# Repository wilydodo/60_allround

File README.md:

I'm making 60% layout keyboard pcb for happyhacking, and other layouts.

can used in dz60 and gh60.

firmware: zmk

used parts
mcu module - E73-2G4M08S1C   
battery charger - TP4054-42-SOT25R   
3.3v regulator - XC6206P332MR-G  
power path diode - BAT54C   
정전기 방지 - SRV05-4A
usb-c -    
도터보드 - Unified Daughterboard   
외부 핀 - 통신용(i2c, spi) 5개, 기타 핀 7개, 전력 3개(gnd, 3v3, 5v)   
추가 핀 커넥터 - JST SH (1.0mm)

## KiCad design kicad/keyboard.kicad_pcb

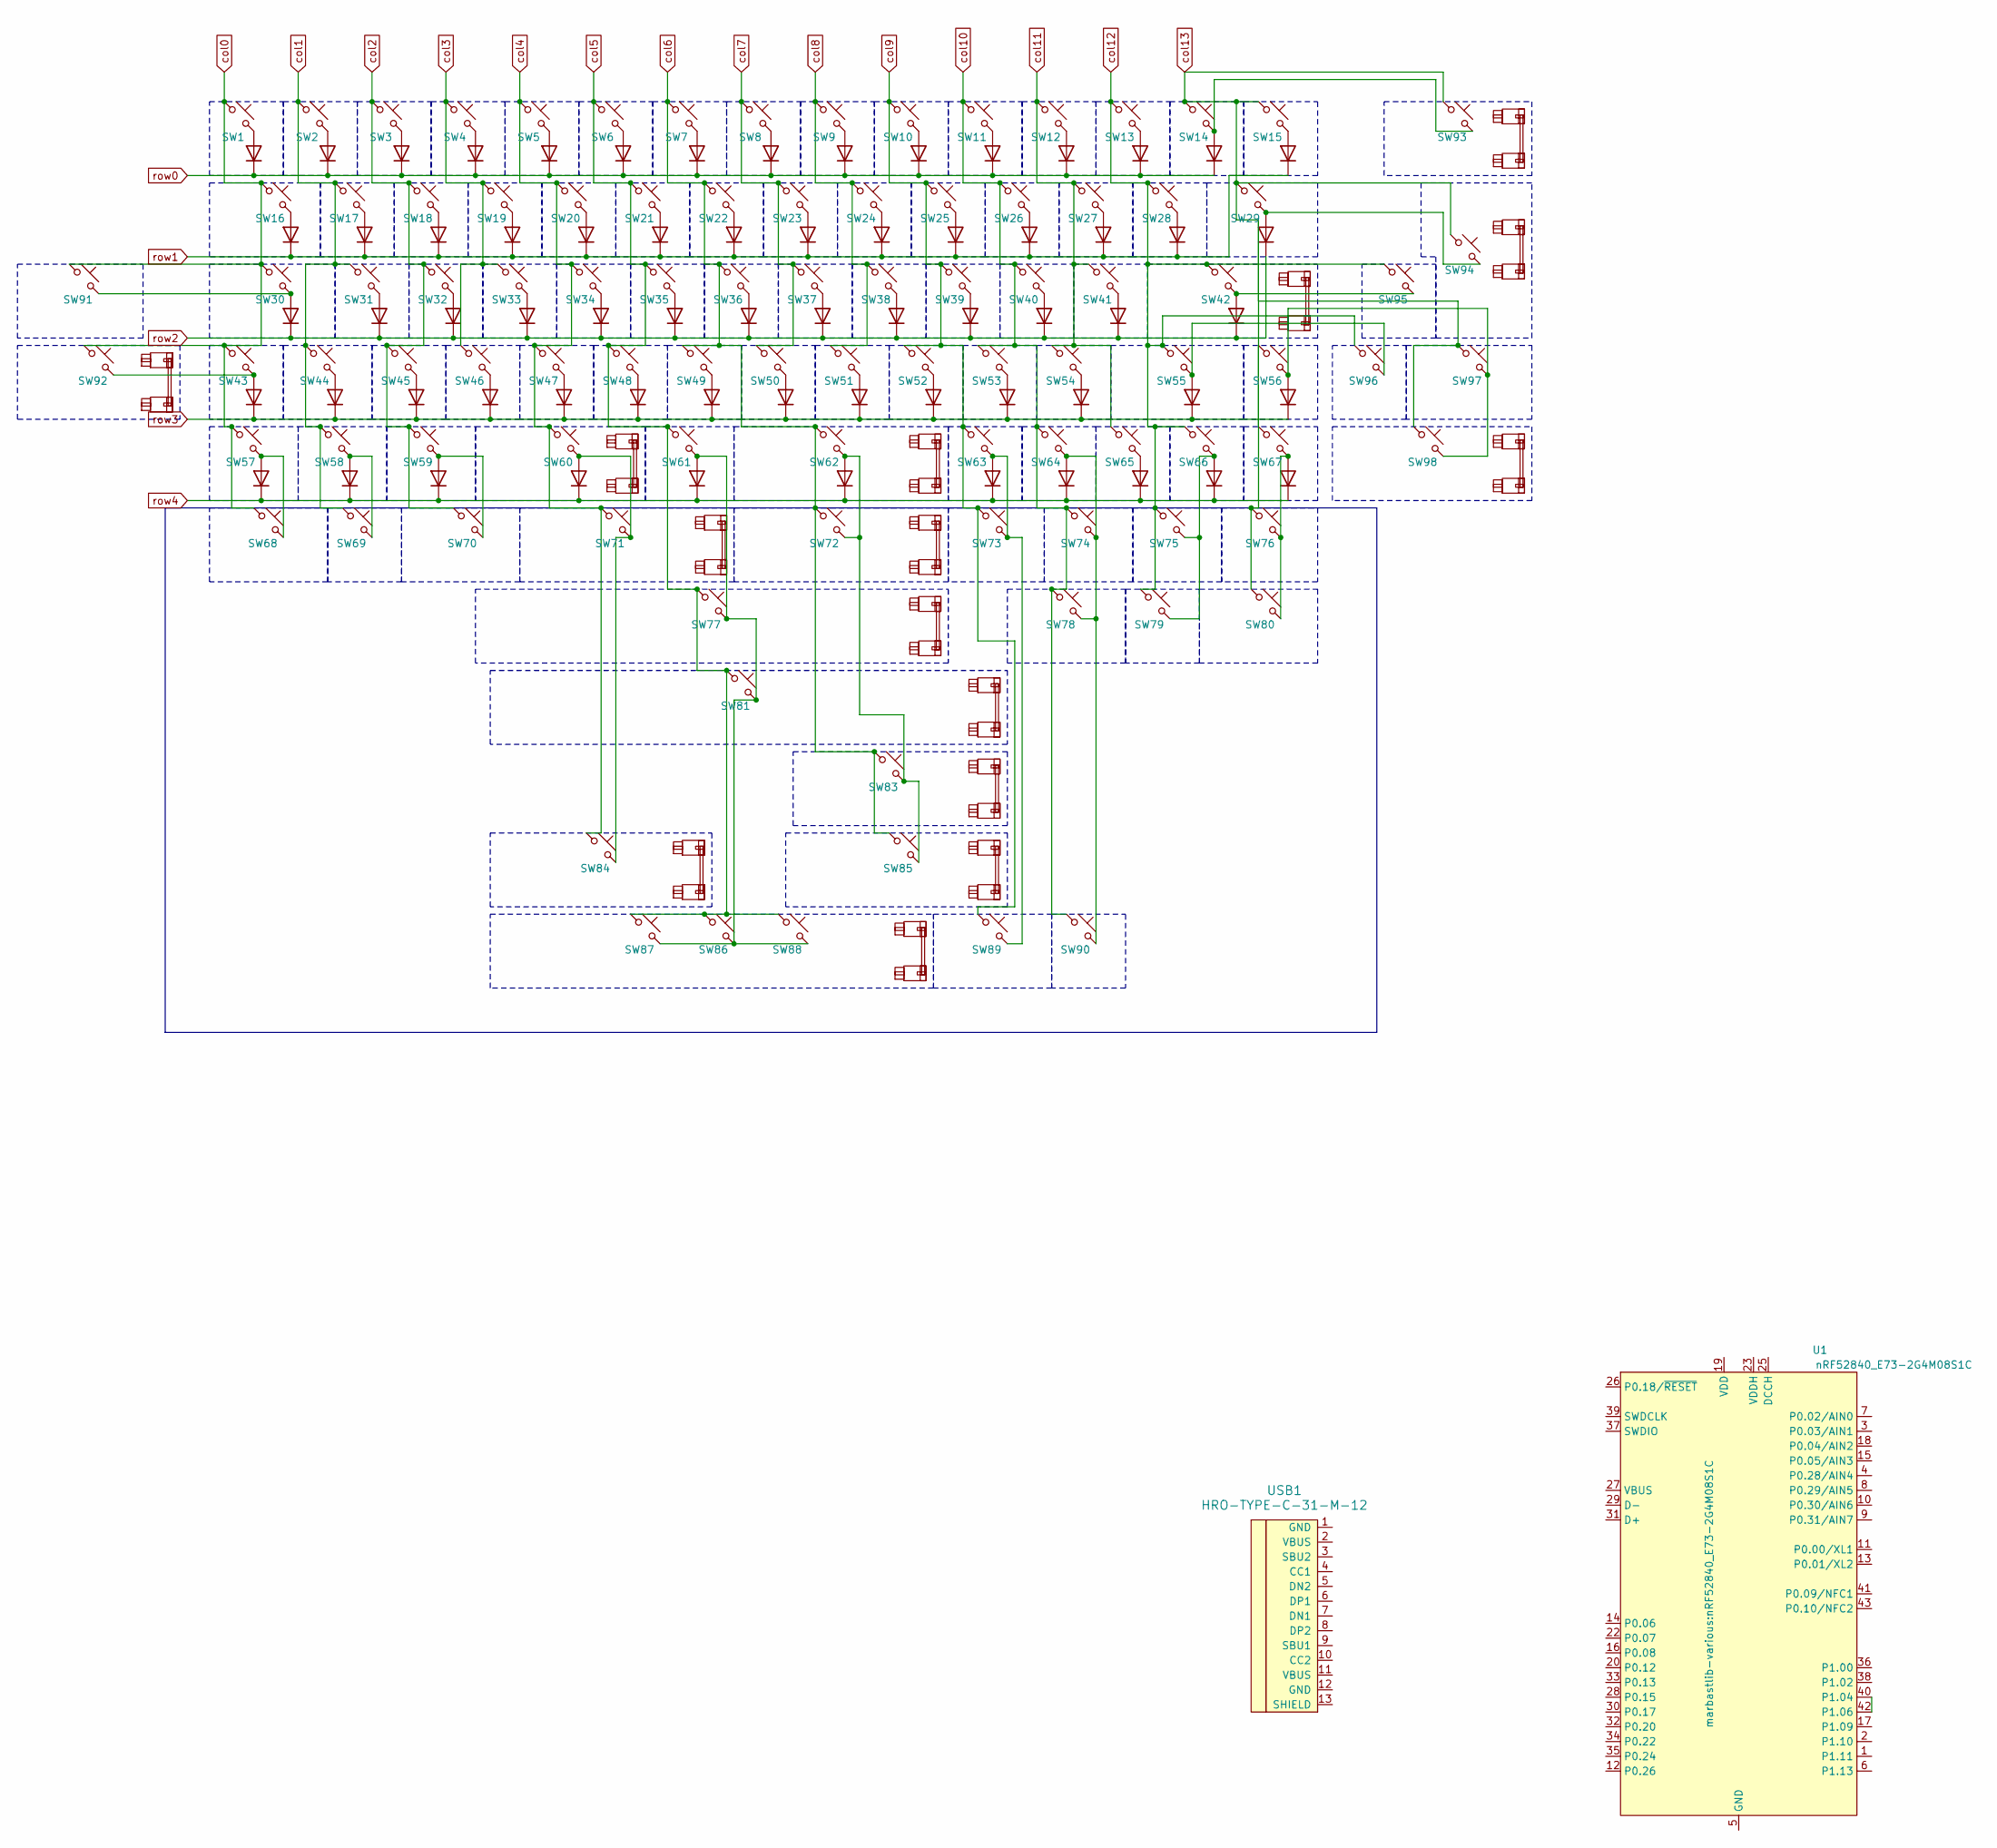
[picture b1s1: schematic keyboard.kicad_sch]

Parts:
D1, D2, D3, D4, D5, D6, D7, D8, D9, D10, D11, D12, D13, D14, D15, D16, D17, D18, D19, D20, D21, D22, D23, D24, D25, D26, D27, D28, D29, D30, D31, D32, D33, D34, D35, D36, D37, D38, D39, D40, D41, D42, D43, D44, D45, D46, D47, D48, D49, D50, D51, D52, D53, D54, D55, D56, D57, D58, D59, D60, D61, D62, D63, D64, D65, D66, D67: 1N4148W; D_SOD-123
S1, S2, S3: MX_stab; STAB_MX_P_2.25u
S4: MX_stab; STAB_MX_P_2u
S5: MX_stab; STAB_MX_P_ISO-ROT
S6, S7, S8, S9, S11: MX_stab; STAB_MX_P_2.75u
S12, S13: MX_stab; STAB_MX_P_3u
S14: MX_stab; STAB_MX_P_6.25u
S15: MX_stab; STAB_MX_P_7u
S16: MX_stab; STAB_MX_P_6u
SW1, SW2, SW3, SW4, SW5, SW6, SW7, SW8, SW9, SW10, SW11, SW12, SW13, SW14, SW15, SW17, SW18, SW19, SW20, SW21, SW22, SW23, SW24, SW25, SW26, SW27, SW28, SW31, SW32, SW33, SW34, SW35, SW36, SW37, SW38, SW39, SW40, SW41, SW42, SW43, SW45, SW46, SW47, SW48, SW49, SW50, SW51, SW52, SW53, SW54, SW56, SW60, SW62, SW63, SW64, SW65, SW66, SW67, SW69, SW71, SW72, SW77, SW79, SW81, SW83, SW84, SW85, SW86, SW87, SW88, SW90, SW91, SW92, SW93, SW94, SW95, SW96, SW98: SW_Push_45deg; SW_MX_1u
SW16, SW29, SW68, SW70, SW78, SW80, SW89: SW_Push_45deg; SW_MX_1.5u
SW30, SW55, SW97: SW_Push_45deg; SW_MX_1.75u
SW44, SW57, SW58, SW59, SW61, SW73, SW74, SW75, SW76: SW_Push_45deg; SW_MX_1.25u
U1: nRF52840_E73-2G4M08S1C; LCSC C356849
USB1: HRO-TYPE-C-31-M-12; HRO-TYPE-C-31-M-12-HandSoldering

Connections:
unnamed: D1.2 (A), SW1.2
unnamed: D2.2 (A), SW2.2
unnamed: D3.2 (A), SW3.2
unnamed: D4.2 (A), SW4.2
unnamed: D5.2 (A), SW5.2
unnamed: D6.2 (A), SW6.2
unnamed: D7.2 (A), SW7.2
unnamed: D8.2 (A), SW8.2
unnamed: D9.2 (A), SW9.2
unnamed: D10.2 (A), SW10.2
unnamed: D11.2 (A), SW11.2
unnamed: D12.2 (A), SW12.2
unnamed: D13.2 (A), SW13.2
unnamed: D14.2 (A), SW14.2, SW93.2
unnamed: D15.2 (A), SW15.2
unnamed: D16.2 (A), SW16.2
unnamed: D17.2 (A), SW17.2
unnamed: D18.2 (A), SW18.2
unnamed: D19.2 (A), SW19.2
unnamed: D20.2 (A), SW20.2
unnamed: D21.2 (A), SW21.2
unnamed: D22.2 (A), SW22.2
unnamed: D23.2 (A), SW23.2
unnamed: D24.2 (A), SW24.2
unnamed: D25.2 (A), SW25.2
unnamed: D26.2 (A), SW26.2
unnamed: D27.2 (A), SW27.2
unnamed: D28.2 (A), SW28.2
unnamed: D29.2 (A), SW29.2, SW94.2
unnamed: D30.2 (A), SW30.2, SW91.2
unnamed: D31.2 (A), SW31.2
unnamed: D32.2 (A), SW32.2
unnamed: D33.2 (A), SW33.2
unnamed: D34.2 (A), SW34.2
unnamed: D35.2 (A), SW35.2
unnamed: D36.2 (A), SW36.2
unnamed: D37.2 (A), SW37.2
unnamed: D38.2 (A), SW38.2
unnamed: D39.2 (A), SW39.2
unnamed: D40.2 (A), SW40.2
unnamed: D41.2 (A), SW41.2
unnamed: D42.2 (A), SW42.2, SW95.2
unnamed: D43.2 (A), SW43.2, SW92.2
unnamed: D44.2 (A), SW44.2
unnamed: D45.2 (A), SW45.2
unnamed: D46.2 (A), SW46.2
unnamed: D47.2 (A), SW47.2
unnamed: D48.2 (A), SW48.2
unnamed: D49.2 (A), SW49.2
unnamed: D50.2 (A), SW50.2
unnamed: D51.2 (A), SW51.2
unnamed: D52.2 (A), SW52.2
unnamed: D53.2 (A), SW53.2
unnamed: D54.2 (A), SW54.2
unnamed: D55.2 (A), SW55.2, SW96.2
unnamed: D56.2 (A), SW56.2, SW97.2, SW98.2
unnamed: D57.2 (A), SW57.2, SW68.2
unnamed: D58.2 (A), SW58.2, SW69.2
unnamed: D59.2 (A), SW59.2, SW70.2
unnamed: D60.2 (A), SW60.2, SW71.2, SW84.2
unnamed: D61.2 (A), SW61.2, SW77.2, SW81.2, SW86.2, SW87.2, SW88.2
unnamed: D62.2 (A), SW62.2, SW72.2, SW83.2, SW85.2
unnamed: D63.2 (A), SW63.2, SW73.2, SW89.2
unnamed: D64.2 (A), SW64.2, SW74.2, SW78.2, SW90.2
unnamed: D65.2 (A), SW65.2
unnamed: D66.2 (A), SW66.2, SW75.2, SW79.2
unnamed: D67.2 (A), SW67.2, SW76.2, SW80.2
unnamed: SW56.1, SW97.1, SW98.1
unnamed: SW67.1, SW76.1, SW80.1
unnamed: U1.5 (GND), U1.21 (GND), U1.24 (GND)
unnamed: U1.40 (P1.04), U1.42 (P1.06)
col0: SW1.1, SW16.1, SW30.1, SW43.1, SW57.1, SW68.1, SW91.1, SW92.1
col1: SW2.1, SW17.1, SW31.1, SW44.1, SW58.1, SW69.1
col2: SW3.1, SW18.1, SW32.1, SW45.1, SW59.1, SW70.1
col3: SW4.1, SW19.1, SW33.1, SW46.1
col4: SW5.1, SW20.1, SW34.1, SW47.1, SW60.1, SW71.1, SW84.1
col5: SW6.1, SW21.1, SW35.1, SW48.1, SW61.1, SW77.1, SW81.1, SW86.1, SW87.1, SW88.1
col6: SW7.1, SW22.1, SW36.1, SW49.1, SW62.1, SW72.1, SW83.1, SW85.1
col7: SW8.1, SW23.1, SW37.1, SW50.1
col8: SW9.1, SW24.1, SW38.1, SW51.1
col9: SW10.1, SW25.1, SW39.1, SW52.1, SW63.1, SW73.1, SW89.1
col10: SW11.1, SW26.1, SW40.1, SW53.1, SW64.1, SW74.1, SW78.1, SW90.1
col11: SW12.1, SW27.1, SW41.1, SW54.1, SW65.1
col12: SW13.1, SW28.1, SW42.1, SW55.1, SW66.1, SW75.1, SW79.1, SW95.1, SW96.1
col13: SW14.1, SW15.1, SW29.1, SW93.1, SW94.1
row0: D1.1 (K), D2.1 (K), D3.1 (K), D4.1 (K), D5.1 (K), D6.1 (K), D7.1 (K), D8.1 (K), D9.1 (K), D10.1 (K), D11.1 (K), D12.1 (K), D13.1 (K), D14.1 (K)
row1: D15.1 (K), D16.1 (K), D17.1 (K), D18.1 (K), D19.1 (K), D20.1 (K), D21.1 (K), D22.1 (K), D23.1 (K), D24.1 (K), D25.1 (K), D26.1 (K), D27.1 (K), D28.1 (K)
row2: D29.1 (K), D30.1 (K), D31.1 (K), D32.1 (K), D33.1 (K), D34.1 (K), D35.1 (K), D36.1 (K), D37.1 (K), D38.1 (K), D39.1 (K), D40.1 (K), D41.1 (K), D42.1 (K)
row3: D43.1 (K), D44.1 (K), D45.1 (K), D46.1 (K), D47.1 (K), D48.1 (K), D49.1 (K), D50.1 (K), D51.1 (K), D52.1 (K), D53.1 (K), D54.1 (K), D55.1 (K), D56.1 (K)
row4: D57.1 (K), D58.1 (K), D59.1 (K), D60.1 (K), D61.1 (K), D62.1 (K), D63.1 (K), D64.1 (K), D65.1 (K), D66.1 (K), D67.1 (K)

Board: 2 copper layers, 188 parts (2 on the bottom side), 90 nets, no tracks yet.

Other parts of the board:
HOLE: VAL**; PKRHC
HOLE#2, HOLE#4, HOLE#5: VAL**; PKRH
HOLE#3, HOLE#6, HOLE#7: VAL**; PKRHSL

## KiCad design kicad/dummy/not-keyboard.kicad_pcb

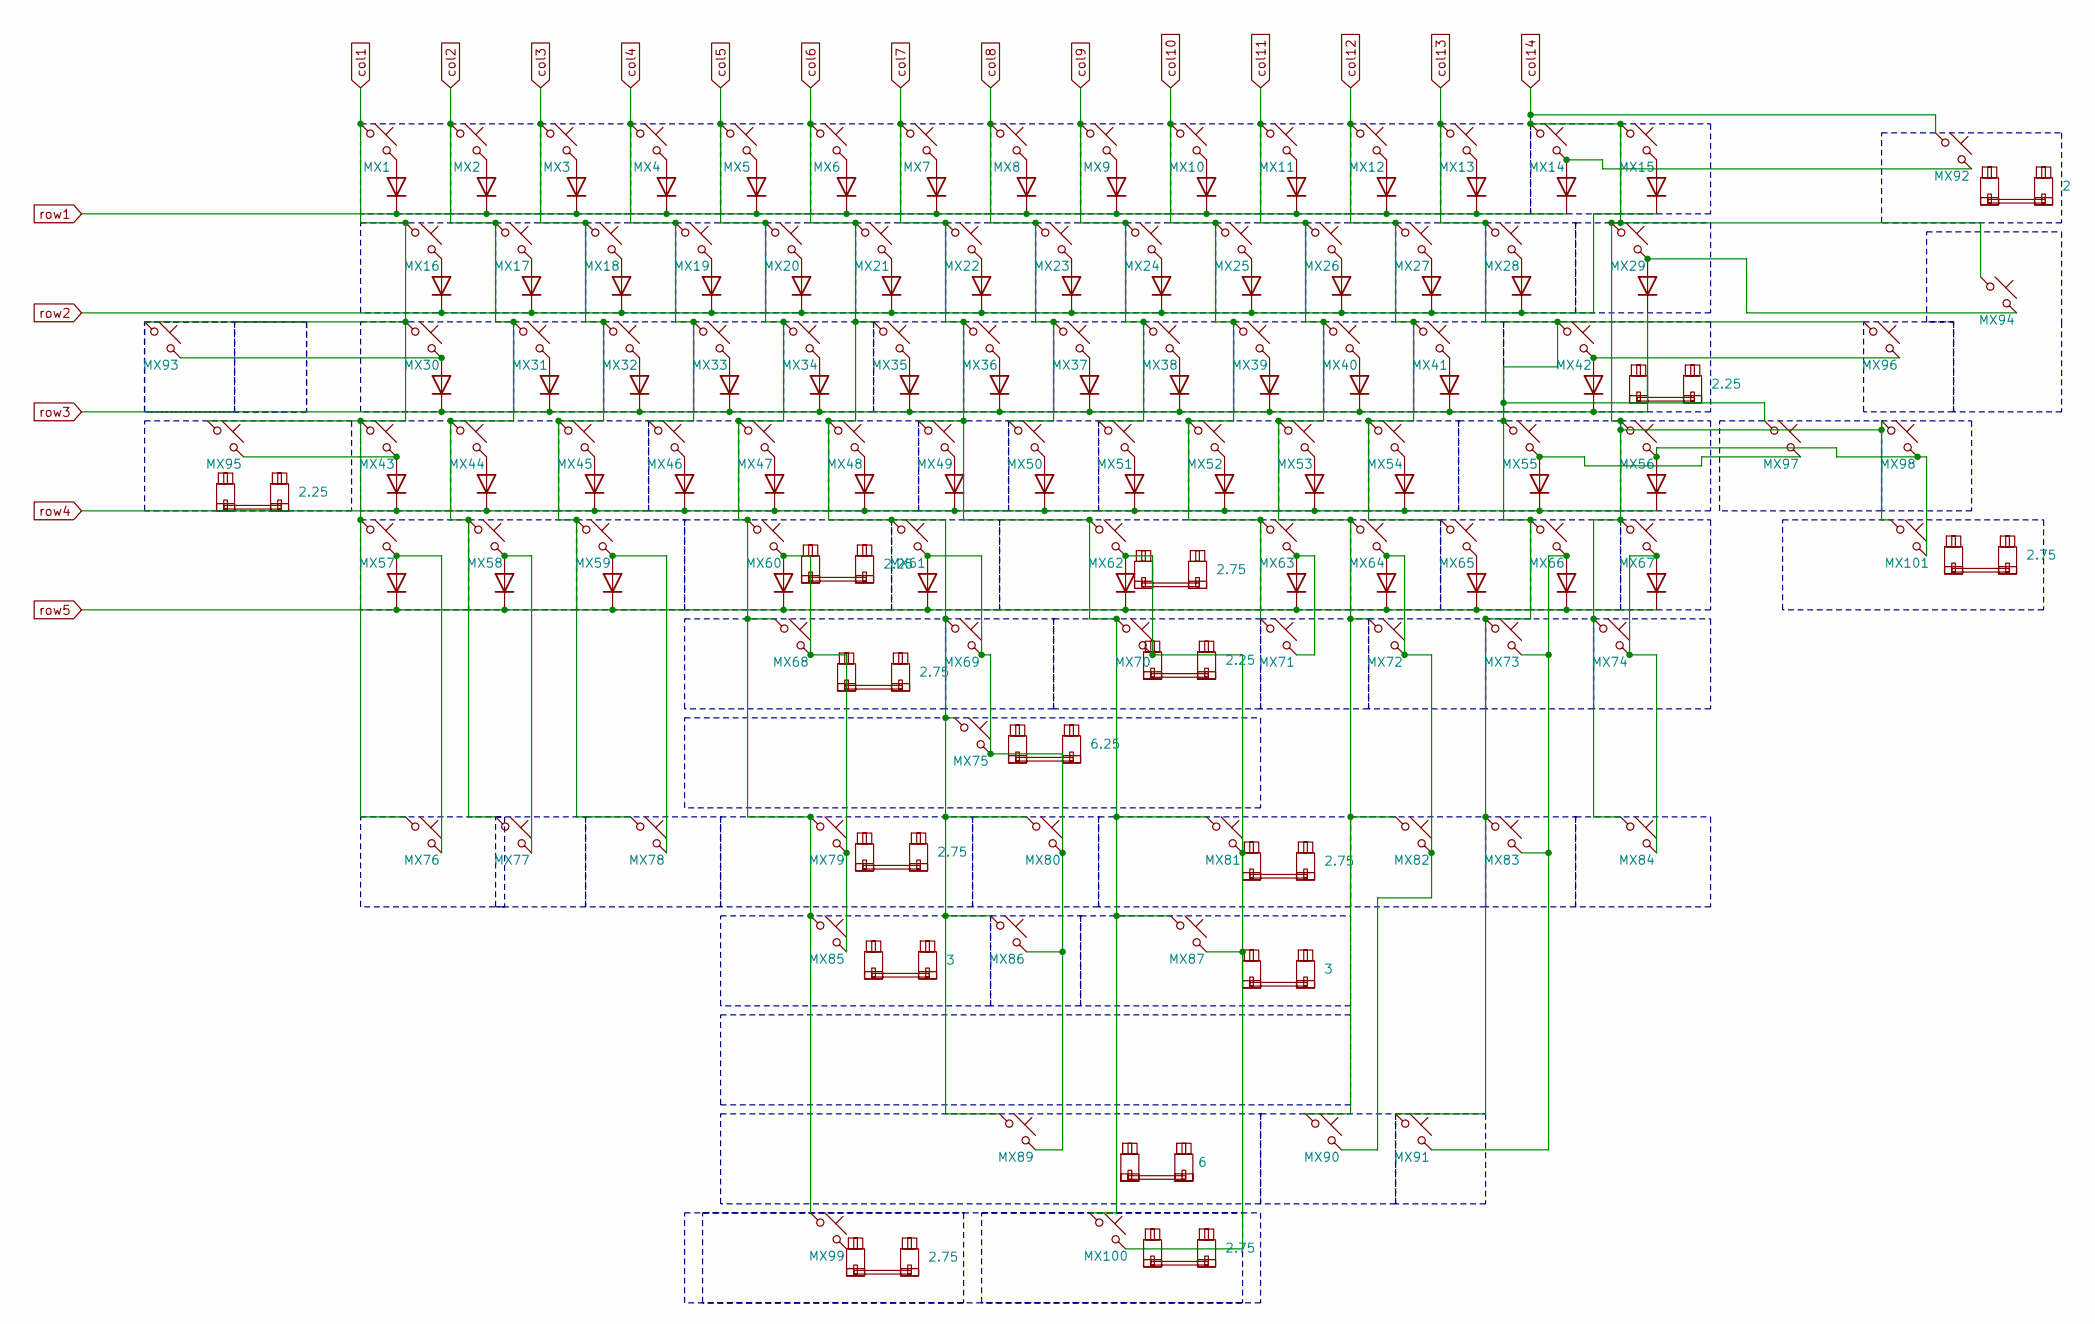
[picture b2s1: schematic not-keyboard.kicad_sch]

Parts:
D1, D2, D3, D4, D5, D6, D7, D8, D9, D10, D11, D12, D13, D14, D15, D16, D17, D18, D19, D20, D21, D22, D23, D24, D25, D26, D27, D28, D29, D30, D31, D32, D33, D34, D35, D36, D37, D38, D39, D40, D41, D42, D43, D44, D45, D46, D47, D48, D49, D50, D51, D52, D53, D54, D55, D56, D57, D58, D59, D60, D61, D62, D63, D64, D65, D66, D67: 1N4148W; D_SOD-123
MX1, MX2, MX3, MX4, MX5, MX6, MX7, MX8, MX9, MX10, MX11, MX12, MX13, MX14, MX15, MX17, MX18, MX19, MX20, MX21, MX22, MX23, MX24, MX25, MX26, MX27, MX28, MX29, MX31, MX32, MX33, MX34, MX35, MX36, MX37, MX38, MX39, MX40, MX41, MX42, MX43, MX45, MX46, MX47, MX48, MX49, MX50, MX51, MX52, MX53, MX54, MX56, MX60, MX62, MX63, MX64, MX65, MX66, MX67, MX68, MX70, MX75, MX77, MX79, MX81, MX83, MX85, MX86, MX87, MX89, MX91, MX92, MX93, MX94, MX95, MX96, MX98, MX99, MX100, MX101: MX_SW_HS; SW_MX_1u
MX16, MX76, MX78, MX80, MX82, MX84, MX90: MX_SW_HS; SW_MX_1.5u
MX30, MX55, MX97: MX_SW_HS; SW_MX_1.75u
MX44, MX57, MX58, MX59, MX61, MX69, MX71, MX72, MX73, MX74: MX_SW_HS; SW_MX_1.25u
S1, S2, S5, S15: 2.25; STAB_MX_P_2.25u
S3, S4, S7, S8, S13, S14, S18: 2.75; STAB_MX_P_2.75u
S6: 6.25; STAB_MX_P_6.25u
S9, S10: 3; STAB_MX_P_3u
S12: 6; STAB_MX_P_6u
S16: 2; STAB_MX_P_2u

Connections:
unnamed: D1.2 (A), MX1.2
unnamed: D2.2 (A), MX2.2
unnamed: D3.2 (A), MX3.2
unnamed: D4.2 (A), MX4.2
unnamed: D5.2 (A), MX5.2
unnamed: D6.2 (A), MX6.2
unnamed: D7.2 (A), MX7.2
unnamed: D8.2 (A), MX8.2
unnamed: D9.2 (A), MX9.2
unnamed: D10.2 (A), MX10.2
unnamed: D11.2 (A), MX11.2
unnamed: D12.2 (A), MX12.2
unnamed: D13.2 (A), MX13.2
unnamed: D14.2 (A), MX14.2, MX92.2
unnamed: D15.2 (A), MX15.2
unnamed: D16.2 (A), MX16.2
unnamed: D17.2 (A), MX17.2
unnamed: D18.2 (A), MX18.2
unnamed: D19.2 (A), MX19.2
unnamed: D20.2 (A), MX20.2
unnamed: D21.2 (A), MX21.2
unnamed: D22.2 (A), MX22.2
unnamed: D23.2 (A), MX23.2
unnamed: D24.2 (A), MX24.2
unnamed: D25.2 (A), MX25.2
unnamed: D26.2 (A), MX26.2
unnamed: D27.2 (A), MX27.2
unnamed: D28.2 (A), MX28.2
unnamed: D29.2 (A), MX29.2, MX94.2
unnamed: D30.2 (A), MX30.2, MX93.2
unnamed: D31.2 (A), MX31.2
unnamed: D32.2 (A), MX32.2
unnamed: D33.2 (A), MX33.2
unnamed: D34.2 (A), MX34.2
unnamed: D35.2 (A), MX35.2
unnamed: D36.2 (A), MX36.2
unnamed: D37.2 (A), MX37.2
unnamed: D38.2 (A), MX38.2
unnamed: D39.2 (A), MX39.2
unnamed: D40.2 (A), MX40.2
unnamed: D41.2 (A), MX41.2
unnamed: D42.2 (A), MX42.2, MX96.2
unnamed: D43.2 (A), MX43.2, MX95.2
unnamed: D44.2 (A), MX44.2
unnamed: D45.2 (A), MX45.2
unnamed: D46.2 (A), MX46.2
unnamed: D47.2 (A), MX47.2
unnamed: D48.2 (A), MX48.2
unnamed: D49.2 (A), MX49.2
unnamed: D50.2 (A), MX50.2
unnamed: D51.2 (A), MX51.2
unnamed: D52.2 (A), MX52.2
unnamed: D53.2 (A), MX53.2
unnamed: D54.2 (A), MX54.2
unnamed: D55.2 (A), MX55.2, MX97.2
unnamed: D56.2 (A), MX56.2, MX98.2, MX101.2
unnamed: D57.2 (A), MX57.2, MX76.2
unnamed: D58.2 (A), MX58.2, MX77.2
unnamed: D59.2 (A), MX59.2, MX78.2
unnamed: D60.2 (A), MX60.2, MX68.2, MX79.2, MX85.2
unnamed: D61.2 (A), MX61.2, MX69.2, MX75.2, MX80.2, MX86.2, MX89.2
unnamed: D62.2 (A), MX62.2, MX70.2, MX81.2, MX87.2, MX100.2
unnamed: D63.2 (A), MX63.2, MX71.2
unnamed: D64.2 (A), MX64.2, MX72.2, MX82.2, MX90.2
unnamed: D65.2 (A), MX65.2
unnamed: D66.2 (A), MX66.2, MX73.2, MX83.2, MX91.2
unnamed: D67.2 (A), MX67.2, MX74.2, MX84.2
col1: MX1.1, MX16.1, MX30.1, MX43.1, MX57.1, MX76.1, MX93.1, MX95.1
col2: MX2.1, MX17.1, MX31.1, MX44.1, MX58.1, MX77.1
col3: MX3.1, MX18.1, MX32.1, MX45.1, MX59.1, MX78.1
col4: MX4.1, MX19.1, MX33.1, MX46.1
col5: MX5.1, MX20.1, MX34.1, MX47.1, MX60.1, MX68.1, MX79.1, MX85.1, MX99.1
col6: MX6.1, MX21.1, MX35.1, MX48.1, MX61.1, MX69.1, MX75.1, MX80.1, MX86.1, MX89.1
col7: MX7.1, MX22.1, MX36.1, MX49.1, MX62.1, MX70.1, MX81.1, MX87.1, MX100.1
col8: MX8.1, MX23.1, MX37.1, MX50.1
col9: MX9.1, MX24.1, MX38.1, MX51.1
col10: MX10.1, MX25.1, MX39.1, MX52.1, MX63.1, MX71.1
col11: MX11.1, MX26.1, MX40.1, MX53.1, MX64.1, MX72.1, MX82.1, MX90.1
col12: MX12.1, MX27.1, MX41.1, MX54.1, MX65.1
col13: MX13.1, MX28.1, MX42.1, MX55.1, MX66.1, MX73.1, MX83.1, MX91.1, MX96.1, MX97.1
col14: MX14.1, MX15.1, MX29.1, MX56.1, MX67.1, MX74.1, MX84.1, MX92.1, MX94.1, MX98.1, MX101.1
row1: D1.1 (K), D2.1 (K), D3.1 (K), D4.1 (K), D5.1 (K), D6.1 (K), D7.1 (K), D8.1 (K), D9.1 (K), D10.1 (K), D11.1 (K), D12.1 (K), D13.1 (K), D14.1 (K)
row2: D15.1 (K), D16.1 (K), D17.1 (K), D18.1 (K), D19.1 (K), D20.1 (K), D21.1 (K), D22.1 (K), D23.1 (K), D24.1 (K), D25.1 (K), D26.1 (K), D27.1 (K), D28.1 (K)
row3: D29.1 (K), D30.1 (K), D31.1 (K), D32.1 (K), D33.1 (K), D34.1 (K), D35.1 (K), D36.1 (K), D37.1 (K), D38.1 (K), D39.1 (K), D40.1 (K), D41.1 (K), D42.1 (K)
row4: D43.1 (K), D44.1 (K), D45.1 (K), D46.1 (K), D47.1 (K), D48.1 (K), D49.1 (K), D50.1 (K), D51.1 (K), D52.1 (K), D53.1 (K), D54.1 (K), D55.1 (K), D56.1 (K)
row5: D57.1 (K), D58.1 (K), D59.1 (K), D60.1 (K), D61.1 (K), D62.1 (K), D63.1 (K), D64.1 (K), D65.1 (K), D66.1 (K), D67.1 (K)

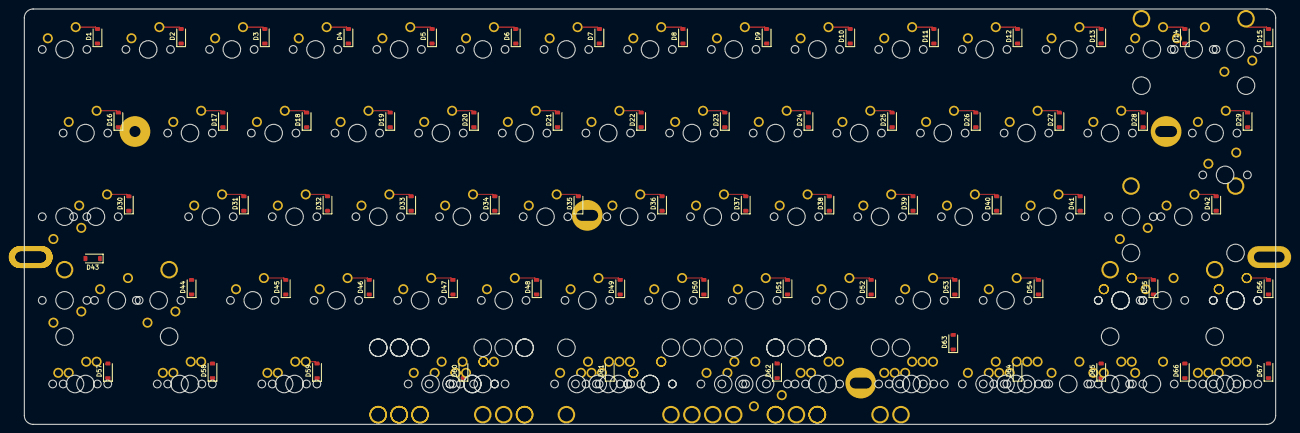
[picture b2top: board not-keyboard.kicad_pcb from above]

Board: 2 copper layers, 285.0 x 94.6 mm, 190 parts (0 on the bottom side), 86 nets.

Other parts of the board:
HOLE: VAL**; PKRHC
HOLE#2, HOLE#4, HOLE#5: VAL**; PKRH
HOLE#3, HOLE#6, HOLE#7: VAL**; PKRHSL

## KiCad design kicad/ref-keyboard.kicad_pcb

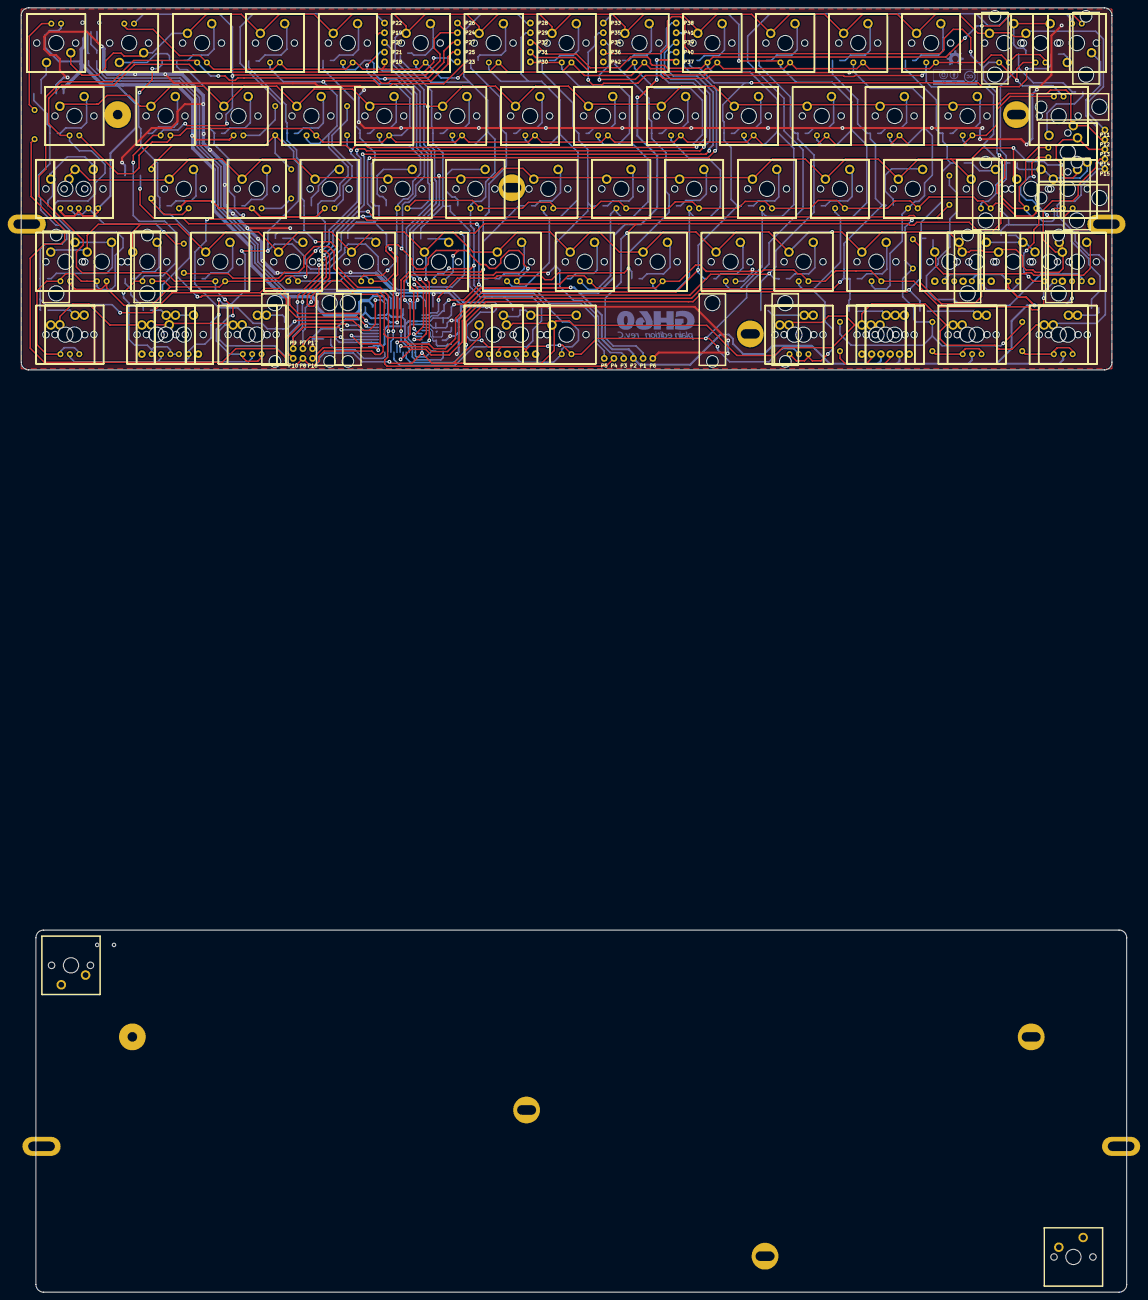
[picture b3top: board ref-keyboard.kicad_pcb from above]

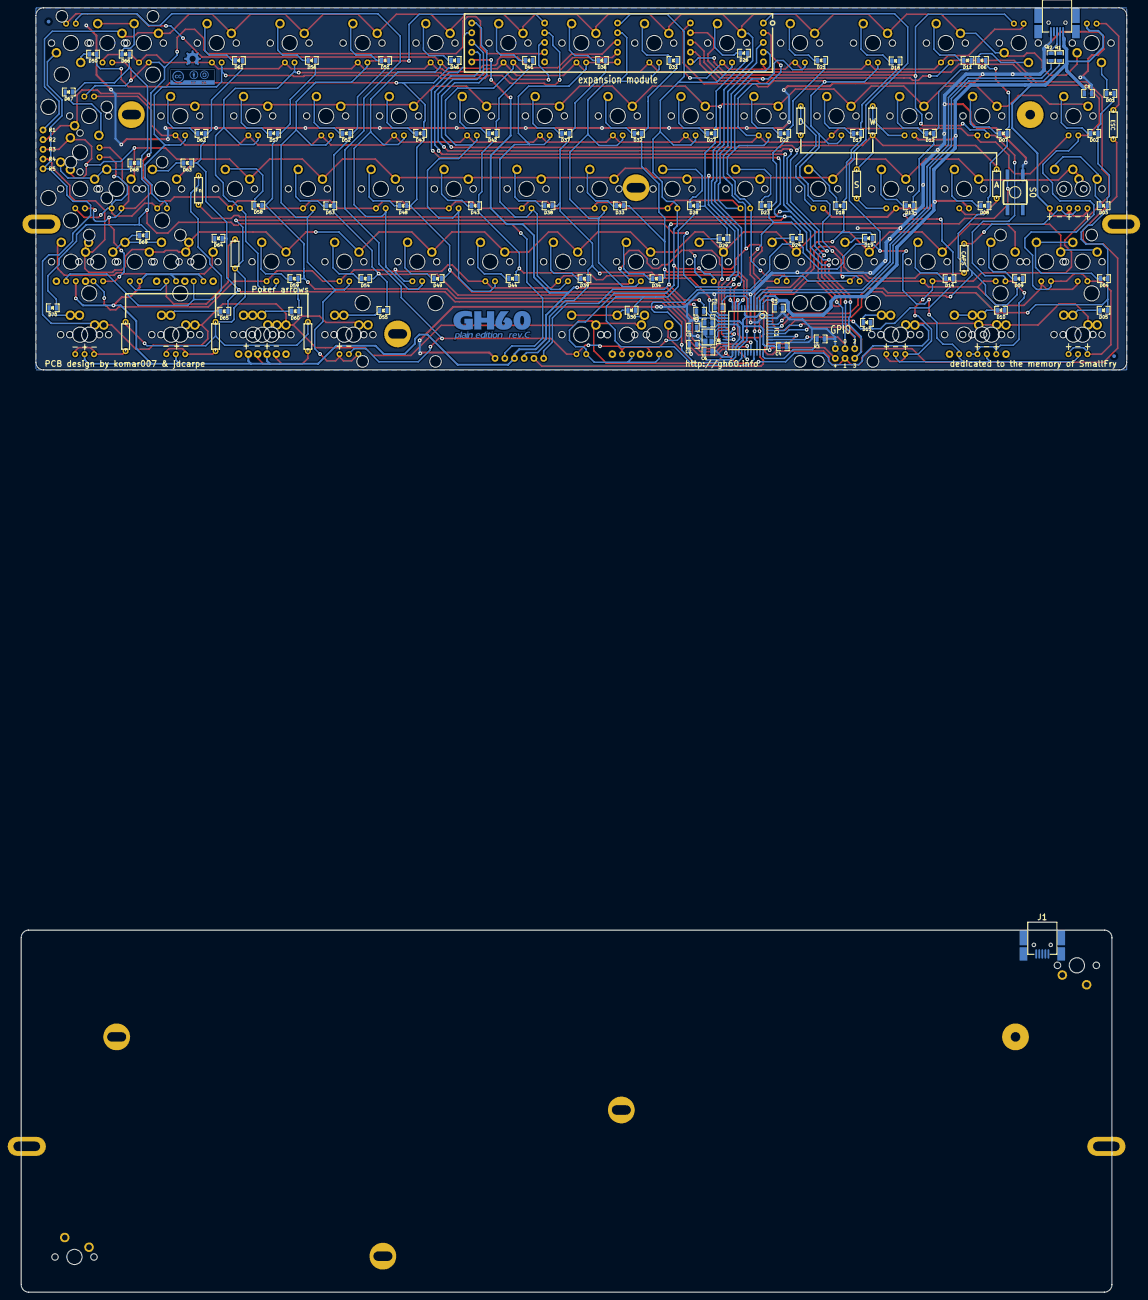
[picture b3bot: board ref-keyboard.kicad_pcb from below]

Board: 2 copper layers, 285.0 x 94.6 mm, 344 parts (95 on the bottom side), 130 nets.

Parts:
C1, C2: 22p; 0805C
C3, C8: 1u; 0805C
C4, C5, C6, C7: 100n; 0805C
D01, D02, D03, D04, D05, D06, D07, D08, D09, D10, D11, D12, D13, D14, D15, D16, D17, D18, D19, D21, D22, D23, D24, D26, D27, D28, D29, D30, D31, D32, D33, D34, D36, D37, D38, D39, D41, D42, D43, D44, D46, D47, D48, D49, D50, D51, D52, D53, D54, D55, D56, D57, D58, D59, D60, D61, D62, D63, D64, D65, D66, D67, D68, D69, D70: 1N4148; 0805D
DB02, DB04, DB06, DB07, DB09, DB11, DB14, DB16, DB17, DB19, DB21, DB22, DB23, DB24, DB26, DB27, DB28, DB29, DB30, DB31, DB32, DB33, DB34, DB36, DB37, DB38, DB39, DB41, DB041, DB42, DB43, DB44, DB46, DB47, DB48, DB49, DB50, DB51, DB52, DB53, DB54, DB56, DB57, DB58, DB59, DB61, DB62, DB63, DB66, DB67, DB68, DB69, DB301, DB302, DB661, DB681, DB682: LED; MX1A-led_no3d
DB05, DB10, DB15, DB051, DB55, DB101, DB102, DB151, DB551: LEDa; MX1A-led
DC1, DC2: LED; MX1A-led_no3d
DC3: LED; MX1A-ledlock
DF3, DF10, DF11, DF20, DF201: LED; MX1A-led_no3d
DF21, DF22, DF23, DF211, DF221, DF231, DF232: LEDa; MX1A-led
DW1, DW2, DW3, DW4: LED; MX1A-led_no3d
FID: FIDUCIAL
FID#2: FIDUCIAL
HOLE: VAL**; PKRHSL
HOLE#2, HOLE#4, HOLE#6, HOLE#8, HOLE#11, HOLE#12: VAL**; PKRH
HOLE#3, HOLE#7, HOLE#9: VAL**; PKRHSL
HOLE#5, HOLE#10: VAL**; PKRHC
IC1: ATMEGA32U4; TQFP44
J1, J1#2: MINI; 67503
MXST: VAL**; MXST
MXST#2, MXST#3, MXST#4, MXST#5, MXST#6, MXST#7, MXST#8, MXST#9, MXST#10, MXST#11, MXST#12, MXST#13, MXST#14, MXST#15: VAL**; MXST
MXWIRE: VAL**; MX1A-wire
MXWIRE#2, MXWIRE#3, MXWIRE#4, MXWIRE#5, MXWIRE#6, MXWIRE#7, MXWIRE#8, MXWIRE#9: VAL**; MX1A-wire
P1, P2, P3, P4, P5, P6, P7, P8, P9, P10, P11, P12, P13, P14, P15, P16, P17, P18, P19, P20, P21, P22, P23, P24, P25, P26, P27, P28, P29, P30, P31, P32, P33, P34, P35, P36, P37, P38, P39, P40, P41, P42: CONN_1; pad
R1, R2: 22; 0805R
R3, R5: 10k; 0805R
R4: 300; resistor
R6, R7, R8, R9, R10, R11, R12, R13, R14, R15: R; resistor
S0: DTSM-6; KSEM31GLFS
S01, S01#2, S02, S03, S04, S05, S06, S07, S08, S10, S11, S12, S13, S14, S15, S16, S17, S18, S19, S21, S22, S23, S24, S26, S27, S28, S29, S30, S31, S32, S33, S34, S36, S37, S38, S39, S41, S42, S43, S44, S46, S47, S48, S49, S51, S52, S53, S54, S55, S56, S57, S58, S59, S60, S61, S62, S65, S66, S67, S68, S69, S70: MX1A
S09, S031, S041, S50, S63, S101, S102, S151, S301, S302, S0512, S552, S601, S602, S641, S661, S682, S691, S692, S6512, S7012, S7012#2: MX1Aa; MX1A_no3d
S64, S681: MX1A; MX1A_no3d
X1: ASX3F; 4-SMD

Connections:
/GPIO0: IC1.36, P7.1, P38.1, R6.1, R7.1, R8.1, R9.1
/GPIO1: IC1.37, P8.1, P39.1, R12.1
/GPIO2: IC1.38, P9.1, P40.1, R10.1
/GPIO3: IC1.39, P10.1, P41.1, R11.1, R13.1, R14.1, R15.1
/Leds/lcol1: DB02.1, DB04.1, DB05.1, DB041.1, DB051.1, P23.1
/Leds/lcol2: DB06.1, DB07.1, DB09.1, DB10.1, DB101.1, DB102.1, P24.1
/Leds/lcol3: DB11.1, DB14.1, DB15.1, DB151.1, P25.1
/Leds/lcol4: DB16.1, DB17.1, DB19.1, P26.1
/Leds/lcol5: DB21.1, DB22.1, DB23.1, DB24.1, P27.1
/Leds/lcol6: DB26.1, DB27.1, DB28.1, DB29.1, DB30.1, DB301.1, DB302.1, P28.1
/Leds/lcol7: DB31.1, DB32.1, DB33.1, DB34.1, P29.1
/Leds/lcol8: DB36.1, DB37.1, DB38.1, DB39.1, P30.1
/Leds/lcol9: DB41.1, DB42.1, DB43.1, DB44.1, P31.1
/Leds/lcol10: DB46.1, DB47.1, DB48.1, DB49.1, DB50.1, P32.1
/Leds/lcol11: DB51.1, DB52.1, DB53.1, DB54.1, DB55.1, DB551.1, P33.1
/Leds/lcol12: DB56.1, DB57.1, DB58.1, DB59.1, P34.1
/Leds/lcol13: DB61.1, DB62.1, DB63.1, P35.1
/Leds/lcol14: DB66.1, DB67.1, DB68.1, DB69.1, DB661.1, DB681.1, DB682.1, P36.1
/Leds/lrow1: DB06.2, DB11.2, DB16.2, DB21.2, DB26.2, DB31.2, DB36.2, DB41.2, DB46.2, DB51.2, DB56.2, DB61.2, DB66.2, DB661.2, P18.1
/Leds/lrow2: DB02.2, DB07.2, DB17.2, DB22.2, DB27.2, DB32.2, DB37.2, DB42.2, DB47.2, DB52.2, DB57.2, DB62.2, DB67.2, P19.1
/Leds/lrow3: DB23.2, DB28.2, DB33.2, DB38.2, DB43.2, DB48.2, DB53.2, DB58.2, DB63.2, DB68.2, DB681.2, DB682.2, P20.1
/Leds/lrow4: DB04.2, DB09.2, DB14.2, DB19.2, DB24.2, DB29.2, DB34.2, DB39.2, DB041.2, DB44.2, DB49.2, DB54.2, DB59.2, DB69.2, P21.1
/Leds/lrow5: DB05.2, DB10.2, DB15.2, DB30.2, DB50.2, DB55.2, DB102.2, DB301.2, DB302.2, P22.1
/Matrix/CAPS_LED: IC1.10, P4.1, R4.2
/Matrix/col1: D01.1, D02.1, D03.1, D04.1, D05.1, IC1.41
/Matrix/col2: D06.1, D07.1, D08.1, D09.1, D10.1, IC1.40
/Matrix/col3: D11.1, D12.1, D13.1, D14.1, D15.1, IC1.1
/Matrix/col4: D16.1, D17.1, D18.1, D19.1, IC1.32
/Matrix/col5: D21.1, D22.1, D23.1, D24.1, IC1.31
/Matrix/col6: D26.1, D27.1, D28.1, D29.1, D30.1, IC1.30
/Matrix/col7: D31.1, D32.1, D33.1, D34.1, IC1.25
/Matrix/col8: D36.1, D37.1, D38.1, D39.1, IC1.9, P3.1
/Matrix/col9: D41.1, D42.1, D43.1, D44.1, IC1.12
/Matrix/col10: D46.1, D47.1, D48.1, D49.1, D50.1, IC1.29
/Matrix/col11: D51.1, D52.1, D53.1, D54.1, D55.1, IC1.28
/Matrix/col12: D56.1, D57.1, D58.1, D59.1, D60.1, IC1.27
/Matrix/col13: D61.1, D62.1, D63.1, D64.1, D65.1, IC1.26
/Matrix/col14: D66.1, D67.1, D68.1, D69.1, D70.1, IC1.11, P1.1
/Matrix/row1: IC1.18, P11.1, S01.1, S06.1, S11.1, S16.1, S21.1, S26.1, S31.1, S36.1, S41.1, S46.1, S51.1, S56.1, S61.1, S66.1, S661.1
/Matrix/row2: IC1.19, P12.1, S02.1, S07.1, S12.1, S17.1, S22.1, S27.1, S32.1, S37.1, S42.1, S47.1, S52.1, S57.1, S62.1, S67.1
/Matrix/row3: IC1.20, P13.1, S03.1, S08.1, S13.1, S18.1, S23.1, S28.1, S031.2, S33.1, S38.1, S43.1, S48.1, S53.1, S58.1, S63.1, S68.1, S681.1, S682.2
/Matrix/row4: IC1.21, P14.1, S04.1, S09.1, S14.1, S19.1, S24.1, S29.1, S34.1, S39.1, S041.1, S44.1, S49.1, S54.1, S59.1, S64.2, S69.1, S641.1, S691.2, S692.1
/Matrix/row5: IC1.22, P15.1, S05.1, S10.1, S15.1, S30.1, S50.1, S55.1, S60.1, S65.1, S70.1, S101.1, S102.1, S151.1, S301.1, S302.1, S0512.1, S552.1, S601.1, S602.1, S6512.1, S7012.1, S7012#2.1
/~RES: IC1.13, P5.1, R5.2, S0.3
GND: C1.2, C2.2, C3.2, C4.2, C5.2, C6.2, C7.2, C8.2, IC1.5, IC1.15, IC1.23, IC1.35, IC1.43, J1.5, J1#2.5, P6.1, P17.1, P42.1, R3.2, S0.1, X1.2, X1.4
unnamed: C1.1, IC1.16, X1.1
unnamed: DW3.2, R8.2
unnamed: DW2.2, R7.2
unnamed: DW1.2, R6.2
unnamed: DW4.2, R9.2
unnamed: IC1.33, R3.1
unnamed: J1.3, J1#2.3, R2.2
unnamed: J1.2, J1#2.2, R1.2
unnamed: IC1.4, R2.1
unnamed: IC1.3, R1.1
unnamed: C3.1, IC1.6
unnamed: C2.1, IC1.17, X1.3
unnamed: DF22.2, DF221.2, R14.2
unnamed: DF3.2, R12.2
unnamed: DF10.2, DF11.2, R10.2
unnamed: DF23.2, DF231.2, R15.2
unnamed: DF20.2, DF201.2, R11.2
unnamed: DF21.2, DF211.2, R13.2
unnamed: D16.2, S16.2
unnamed: D27.2, S27.2
unnamed: D28.2, S28.2
unnamed: D29.2, S29.2
unnamed: D17.2, S17.2
unnamed: D18.2, S18.2
unnamed: D19.2, S19.2
unnamed: D41.2, S41.2
unnamed: D37.2, S37.2
unnamed: D38.2, S38.2
unnamed: D22.2, S22.2
unnamed: D43.2, S43.2
unnamed: D42.2, S42.2
unnamed: D46.2, S46.2
unnamed: D47.2, S47.2
unnamed: D23.2, S23.2
unnamed: D21.2, S21.2
unnamed: D31.2, S31.2
unnamed: D01.2, S01.2
unnamed: D33.2, S33.2
unnamed: D32.2, S32.2
unnamed: D36.2, S36.2
unnamed: D05.2, S05.2, S0512.2
unnamed: D15.2, S15.2, S151.2
unnamed: D55.2, S55.2, S552.2
unnamed: D51.2, S51.2
unnamed: D65.2, S65.2, S6512.2
unnamed: D12.2, S12.2
unnamed: D02.2, S02.2
unnamed: D07.2, S07.2
unnamed: D08.2, S08.2
unnamed: D13.2, S13.2
unnamed: D09.2, S09.2
unnamed: D14.2, S14.2
unnamed: D70.2, S70.2, S7012.2, S7012#2.2
unnamed: D03.2, S03.2, S031.1
unnamed: D26.2, S26.2
unnamed: D06.2, S06.2
unnamed: D11.2, S11.2
unnamed: D50.2, S50.2
unnamed: D63.2, S63.2
unnamed: D58.2, S58.2
unnamed: D53.2, S53.2
unnamed: D67.2, S67.2
unnamed: D52.2, S52.2
unnamed: D48.2, S48.2
unnamed: D44.2, S44.2
unnamed: D62.2, S62.2
unnamed: D49.2, S49.2
unnamed: D54.2, S54.2
unnamed: D59.2, S59.2
unnamed: D57.2, S57.2
unnamed: D61.2, S61.2
unnamed: D56.2, S56.2
unnamed: D24.2, S24.2
unnamed: D34.2, S34.2
unnamed: D39.2, S39.2
unnamed: D68.2, S68.2, S681.2, S682.1
unnamed: D10.2, S10.2, S101.2, S102.2
unnamed: D30.2, S30.2, S301.2, S302.2
unnamed: D04.2, S04.2, S041.2
unnamed: D64.2, S64.1, S641.2
unnamed: D69.2, S69.2, S691.1, S692.2
unnamed: DC1.2, DC2.2, R4.1
unnamed: D60.2, S60.2, S601.2, S602.2
unnamed: D66.2, S66.2, S661.2
VCC: C4.1, C5.1, C6.1, C7.1, C8.1, DC1.1, DC2.1, DC3.1, DF3.1, DF10.1, DF11.1, DF20.1, DF21.1, DF22.1, DF23.1, DF201.1, DF232.1, DW1.1, DW2.1, DW3.1, DW4.1, IC1.2, IC1.7, IC1.14, IC1.24, IC1.34, IC1.44, J1.1, J1#2.1, P2.1, P16.1, P37.1, R5.1

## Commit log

2025-12-29 start to write parts info
2025-12-31 Update README.md
    enter test
2025-12-31 Update README.md
    roll-back
2025-12-31 Update parts data
2026-01-07 Update README with Unified Daughterboard details
    Added information about Unified Daughterboard and ZMK usage.
2026-01-08 Create lowdata
2026-01-08 Update and rename lowdata to rawdata
2026-01-08 add image file
2026-01-08 start to record
2026-01-10 Update rawdata
2026-01-10 Create 2026-01-10
